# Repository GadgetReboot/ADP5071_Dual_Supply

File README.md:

# ADP5071_Dual_Supply
+5V to  +/- 12V Switching Power Supply
<br><br><BR><BR>

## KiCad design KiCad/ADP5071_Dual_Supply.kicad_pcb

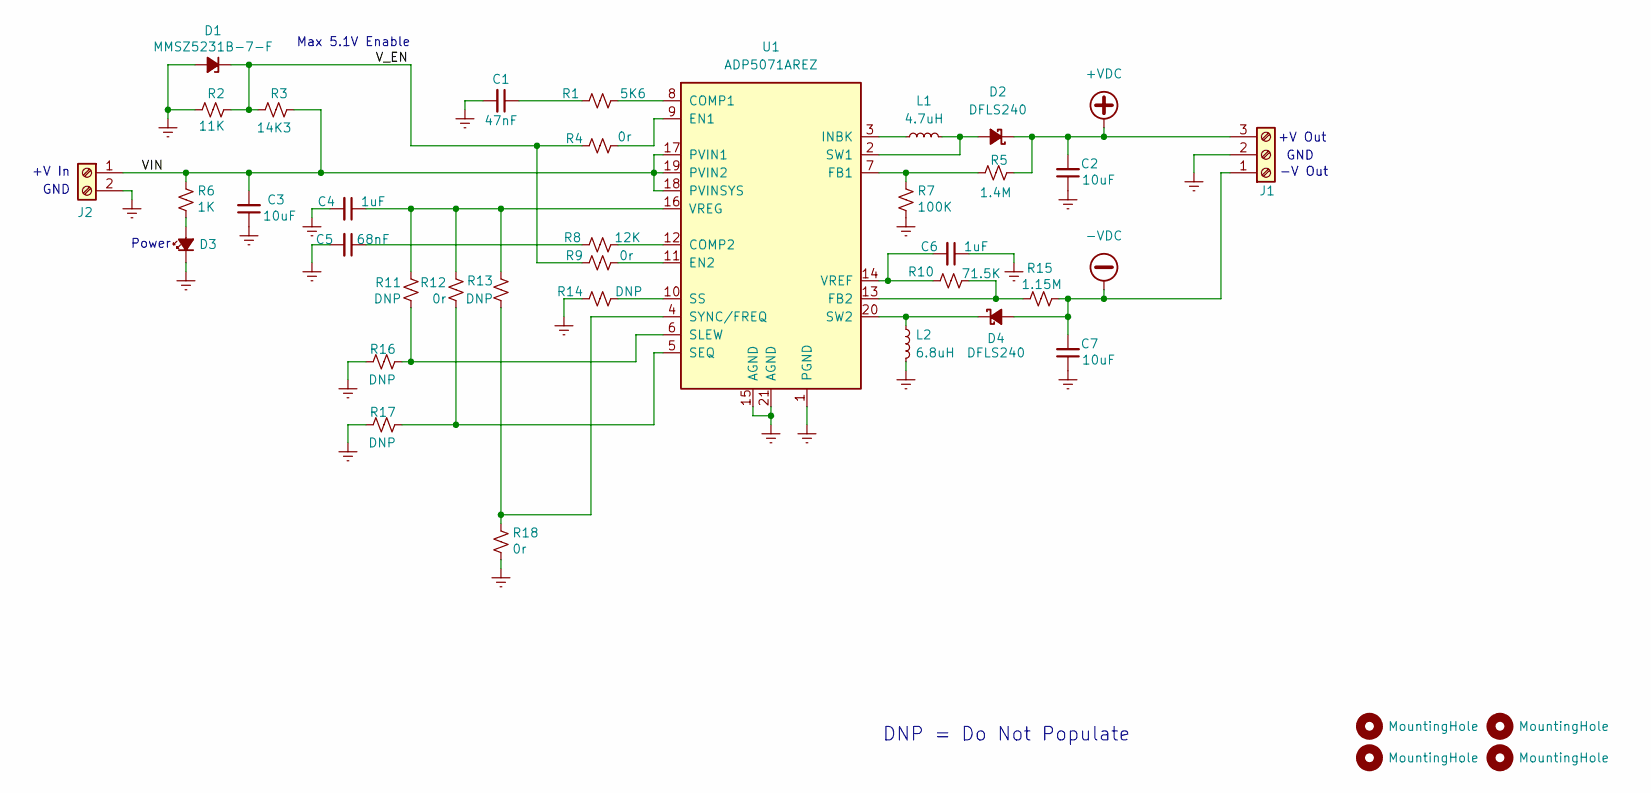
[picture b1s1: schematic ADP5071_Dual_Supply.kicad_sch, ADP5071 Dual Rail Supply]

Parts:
C1: 47nF; C_0805_2012Metric_Pad1.18x1.45mm_HandSolder
C2, C3, C7: 10uF; C_1210_3225Metric_Pad1.33x2.70mm_HandSolder
C4, C6: 1uF; C_0805_2012Metric_Pad1.18x1.45mm_HandSolder
C5: 68nF; C_0805_2012Metric_Pad1.18x1.45mm_HandSolder
D1: MMSZ5231B-7-F; D_SOD-123
D2, D4: DFLS240; D_PowerDI-123
D3: LED_Small_Filled; LED_0805_2012Metric_Pad1.15x1.40mm_HandSolder
H1, H2, H3, H4: MountingHole; MountingHole_3.5mm
J1: Screw_Terminal_01x03; TerminalBlock_CUI_TB007-508-03_1x03_P5.08mm_Horizontal
J2: Screw_Terminal_01x02; TerminalBlock_CUI_TB007-508-02_1x02_P5.08mm_Horizontal
L1: 4.7uH; L_Coilcraft_XAL4030-XXX
L2: 6.8uH; L_Coilcraft_XAL4030-XXX
R1: 5K6; R_0805_2012Metric_Pad1.20x1.40mm_HandSolder
R2: 11K; R_0805_2012Metric_Pad1.20x1.40mm_HandSolder
R3: 14K3; R_0805_2012Metric_Pad1.20x1.40mm_HandSolder
R4, R9, R12, R18: 0r; R_0805_2012Metric_Pad1.20x1.40mm_HandSolder
R5: 1.4M; R_0805_2012Metric_Pad1.20x1.40mm_HandSolder
R6: 1K; R_0805_2012Metric_Pad1.20x1.40mm_HandSolder
R7: 100K; R_0805_2012Metric_Pad1.20x1.40mm_HandSolder
R8: 12K; R_0805_2012Metric_Pad1.20x1.40mm_HandSolder
R10: 71.5K; R_0805_2012Metric_Pad1.20x1.40mm_HandSolder
R11, R13, R14, R16, R17: DNP; R_0805_2012Metric_Pad1.20x1.40mm_HandSolder
R15: 1.15M; R_0805_2012Metric_Pad1.20x1.40mm_HandSolder
U1: ADP5071AREZ; ETSSOP-20-1EP_4.4x6.5mm_P0.65mm_EP3x4.2mm

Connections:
+VDC: C2.2, D2.1 (K), J1.3, R5.2
-VDC: C7.2, D4.2 (A), J1.1, R15.2
/VIN: C3.2, J2.1, R3.2, R6.1, U1.17 (PVIN1), U1.18 (PVINSYS), U1.19 (PVIN2)
/V_EN: D1.1 (K), R2.2, R3.1, R4.1, R9.1
GNDREF: C1.2, C2.1, C3.1, C4.2, C5.2, C6.1, C7.1, D1.2 (A), D3.1 (K), J1.2, J2.2, L2.2, R2.1, R7.2, R14.1, R16.1, R17.1, R18.2, U1.1 (PGND), U1.15 (AGND), U1.21 (AGND)
unnamed: C1.1, R1.1
unnamed: C5.1, R8.1
unnamed: D2.2 (A), L1.2, U1.2 (SW1)
unnamed: D3.2 (A), R6.2
unnamed: D4.1 (K), L2.1, U1.20 (SW2)
unnamed: R1.2, U1.8 (COMP1)
unnamed: R8.2, U1.12 (COMP2)
unnamed: R4.2, U1.9 (EN1)
unnamed: R9.2, U1.11 (EN2)
unnamed: R5.1, R7.1, U1.7 (FB1)
unnamed: R10.2, R15.1, U1.13 (FB2)
unnamed: L1.1, U1.3 (INBK)
unnamed: R12.1, R17.2, U1.5 (SEQ)
unnamed: R11.1, R16.2, U1.6 (SLEW)
unnamed: R14.2, U1.10 (SS)
unnamed: R13.1, R18.1, U1.4 (SYNC/FREQ)
unnamed: C6.2, R10.1, U1.14 (VREF)
unnamed: C4.1, R11.2, R12.2, R13.2, U1.16 (VREG)

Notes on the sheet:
GND
+V In
DNP = Do Not Populate
-V Out
Max 5.1V Enable
+V Out
Power

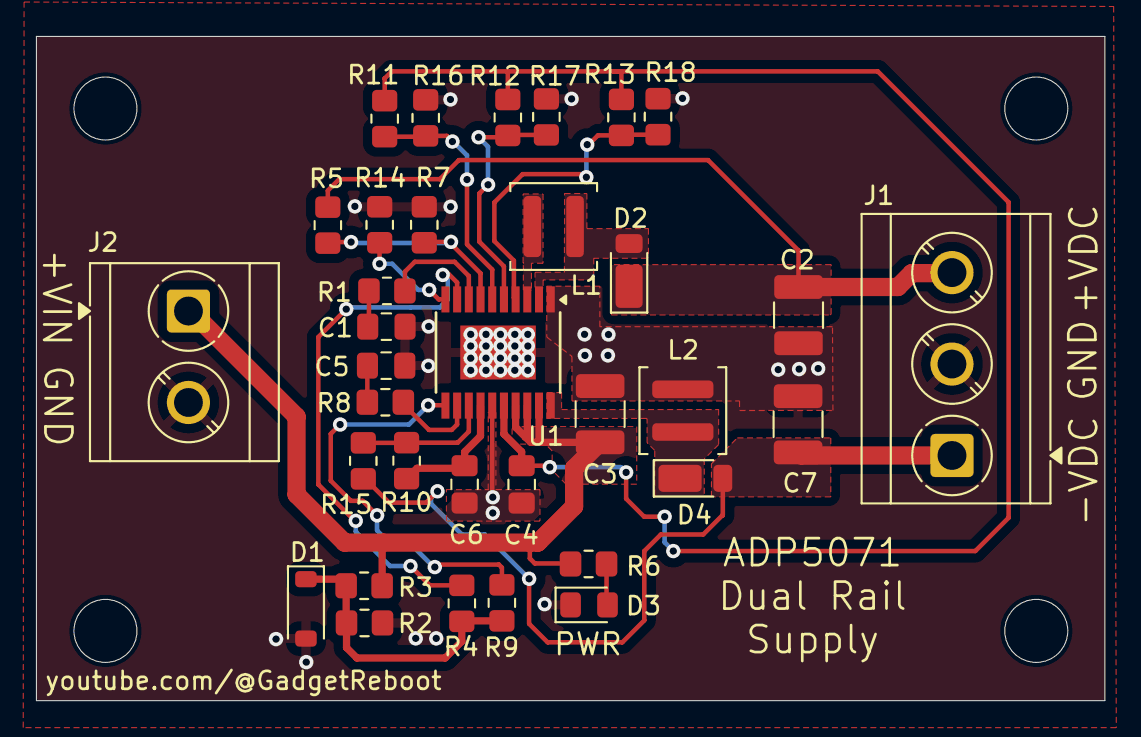
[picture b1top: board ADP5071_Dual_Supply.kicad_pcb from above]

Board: 2 copper layers, 59.4 x 36.9 mm, 38 parts (0 on the bottom side), 23 nets.
